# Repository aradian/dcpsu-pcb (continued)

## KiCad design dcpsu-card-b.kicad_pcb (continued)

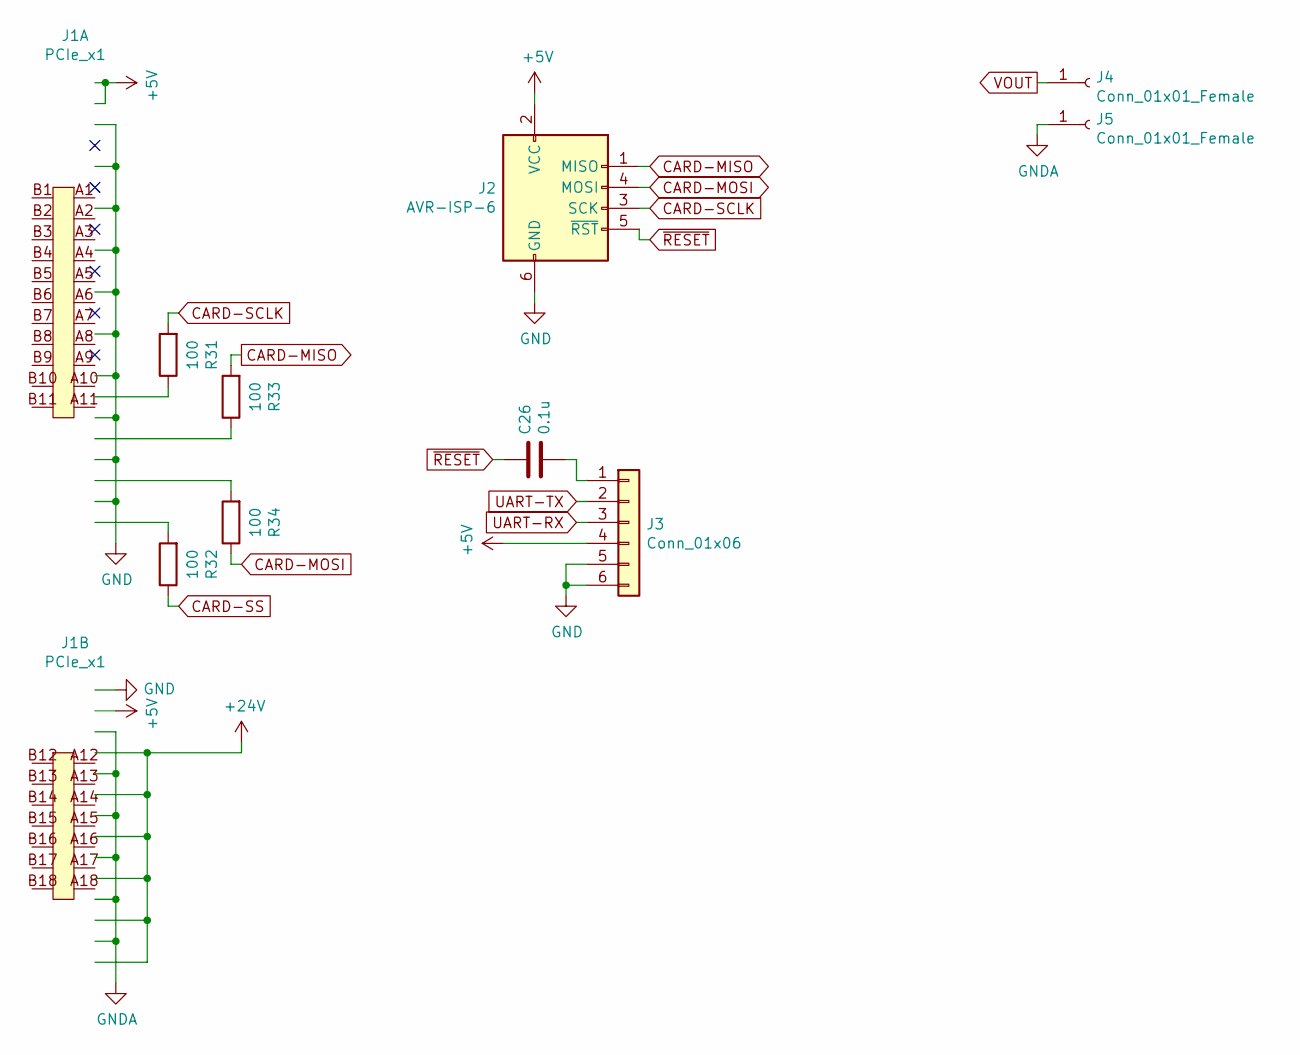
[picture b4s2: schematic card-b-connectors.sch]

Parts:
C26: 0.1u; C_0603_1608Metric_Pad1.05x0.95mm_HandSolder; Digi-Key_PN 399-1099-1-ND
J1: PCIe_x1; BUS_PCIexpress
J2: AVR-ISP-6; IDC-Header_2x03_P2.54mm_Vertical; Digi-Key_PN 609-2845-ND
J3: Conn_01x06; PinHeader_1x06_P2.54mm_Vertical
J4, J5: Conn_01x01_Female; SolderWirePad_1x01_Drill1.5mm
R31, R32, R33, R34: 100; R_0603_1608Metric_Pad1.05x0.95mm_HandSolder; Digi-Key_PN RMCF0603JT100RCT-ND

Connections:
+5V: J1.A1, J1.B1, J1.B12, J2.2 (VCC), J3.4; also elsewhere on the board
+24V: J1.B13, J1.B14, J1.B15, J1.B16, J1.B17, J1.B18; also elsewhere on the board
CARD-MISO: J2.1 (MISO), R33.2; also elsewhere on the board
CARD-MOSI: J2.4 (MOSI), R34.1; also elsewhere on the board
CARD-SCLK: J2.3 (SCK), R31.2; also elsewhere on the board
CARD-SS: R32.1; also elsewhere on the board
GND: J1.A2, J1.A3, J1.A4, J1.A5, J1.A6, J1.A7, J1.A8, J1.A9, J1.A10, J1.A11, J1.A12, J1.A13, J1.A14, J1.A15, J1.A16, J1.A17, J1.A18, J2.6 (GND), J3.5, J3.6, J5.1; also elsewhere on the board
unnamed: C26.2, J3.1
unnamed: J1.B8, R31.1
unnamed: J1.B9, R33.1
unnamed: J1.B10, R34.2
unnamed: J1.B11, R32.2
UART-RX: J3.3; also elsewhere on the board
UART-TX: J3.2; also elsewhere on the board
VOUT: J4.1; also elsewhere on the board
~RESET: C26.1, J2.5 (~RST); also elsewhere on the board

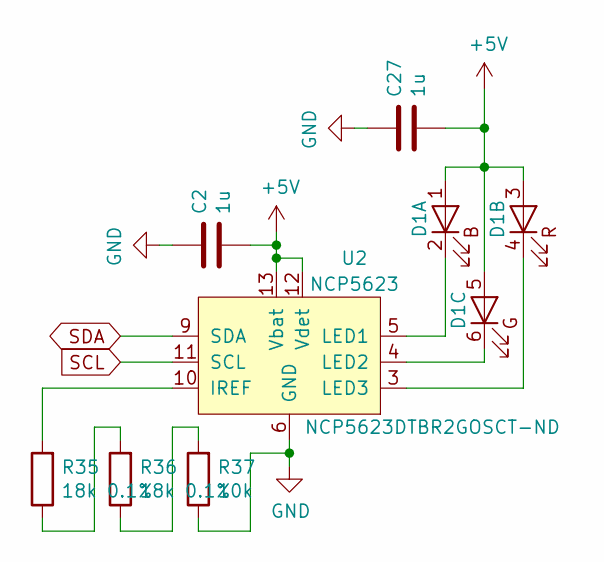
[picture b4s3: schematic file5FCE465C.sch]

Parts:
C2, C27: 1u; C_0603_1608Metric_Pad1.05x0.95mm_HandSolder; Digi-Key_PN 399-7847-1-ND
D1: QLS6B-FKW; Digi-Key_PN QLS6B-FKW-CNSNSF043CT-ND
R35, R36: 18k 0.1%; R_0603_1608Metric_Pad1.05x0.95mm_HandSolder; Digi-Key_PN P20113CT-ND
R37: 10k; R_0603_1608Metric_Pad1.05x0.95mm_HandSolder; Digi-Key_PN RMCF0603JT10K0CT-ND
U2: NCP5623; TSSOP-14_W4.4mm; Digi-Key_PN NCP5623DTBR2GOSCT-ND

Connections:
+5V: C2.2, C27.2, D1.1 (B_A), D1.3 (R_A), D1.5 (G_A), U2.12 (Vdet), U2.13 (Vbat); also elsewhere on the board
GND: C2.1, C27.1, R37.1, U2.2 (GND), U2.6 (GND); also elsewhere on the board
unnamed: D1.2 (B_K), U2.5 (LED1)
unnamed: D1.4 (R_K), U2.3 (LED3)
unnamed: D1.6 (G_K), U2.4 (LED2)
unnamed: R35.1, R36.2
unnamed: R35.2, U2.10 (IREF)
unnamed: R36.1, R37.2
SCL: U2.11 (SCL); also elsewhere on the board
SDA: U2.9 (SDA); also elsewhere on the board

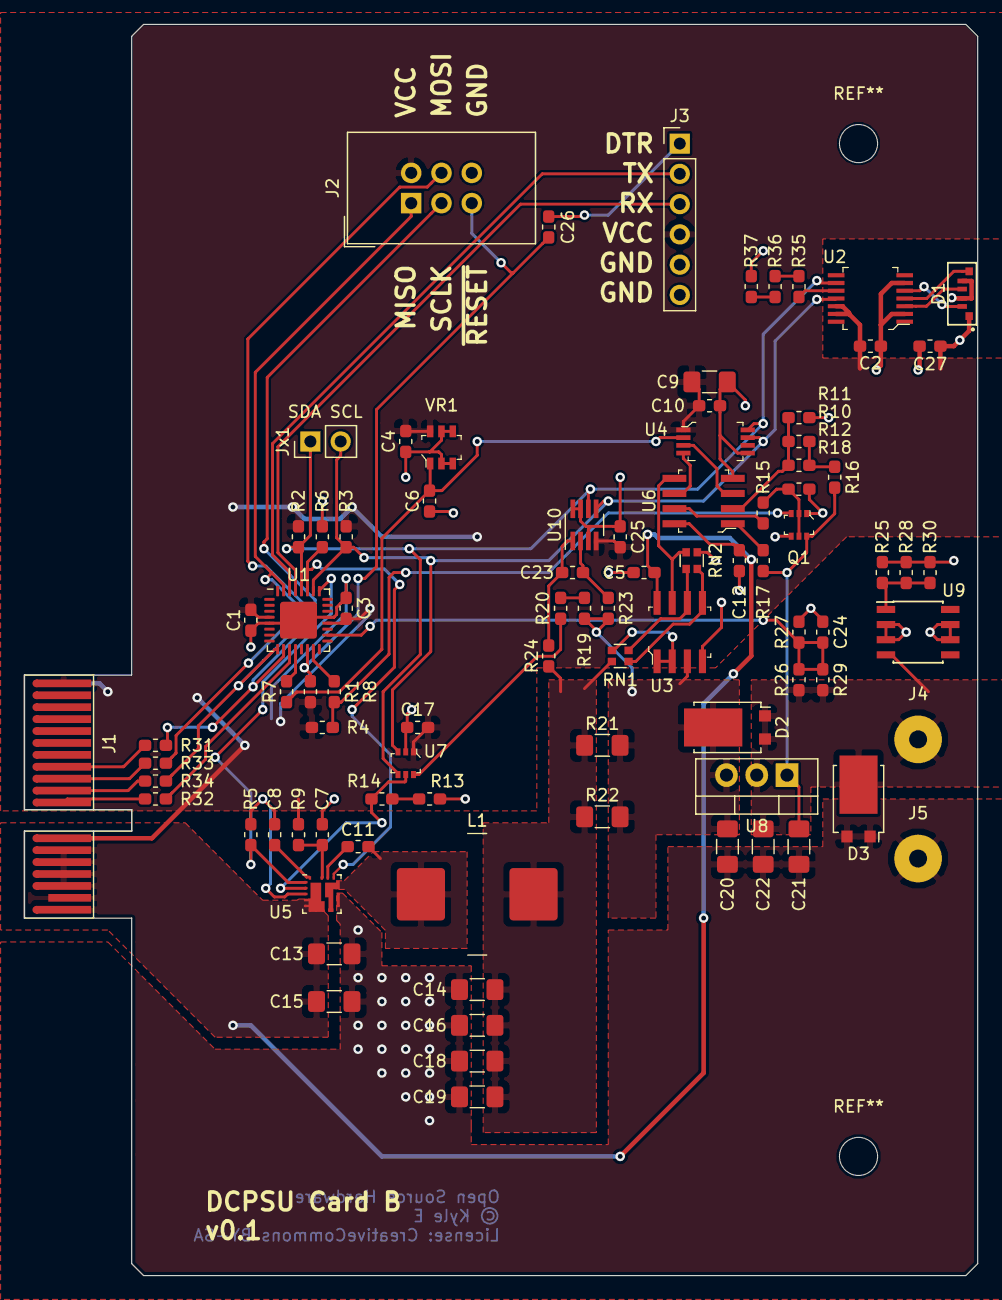
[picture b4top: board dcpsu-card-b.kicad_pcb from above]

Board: 2 copper layers, 80.0 x 105.0 mm, 88 parts (0 on the bottom side), 56 nets.

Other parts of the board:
Jx1: PinHeader_1x02_P2.54mm_Vertical
R9: 2k; R_0603_1608Metric_Pad1.05x0.95mm_HandSolder

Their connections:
+5V: R9.1; also elsewhere on the board
unnamed 16: R9.2; also elsewhere on the board
SCL: Jx1.2; also elsewhere on the board
SDA: Jx1.1; also elsewhere on the board

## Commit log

2020-09-04 Add existing project
2020-11-02 Card A Rev 0.3
2020-11-22 Update README.md
    Add Desmos links.
2021-01-31 Update with notes and pending changes
2021-02-01 Card A v0.4-WIP
2021-03-02 Update Card A (v0.4-WIP)
